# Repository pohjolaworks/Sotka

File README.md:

# Sotka

Split mechanical keyboard with orthogonal layout and detachable extra row

Uses an RJ12 cable for serial communication between the halves.

### Basic layout without extra row

### Reversible PCB with extra row

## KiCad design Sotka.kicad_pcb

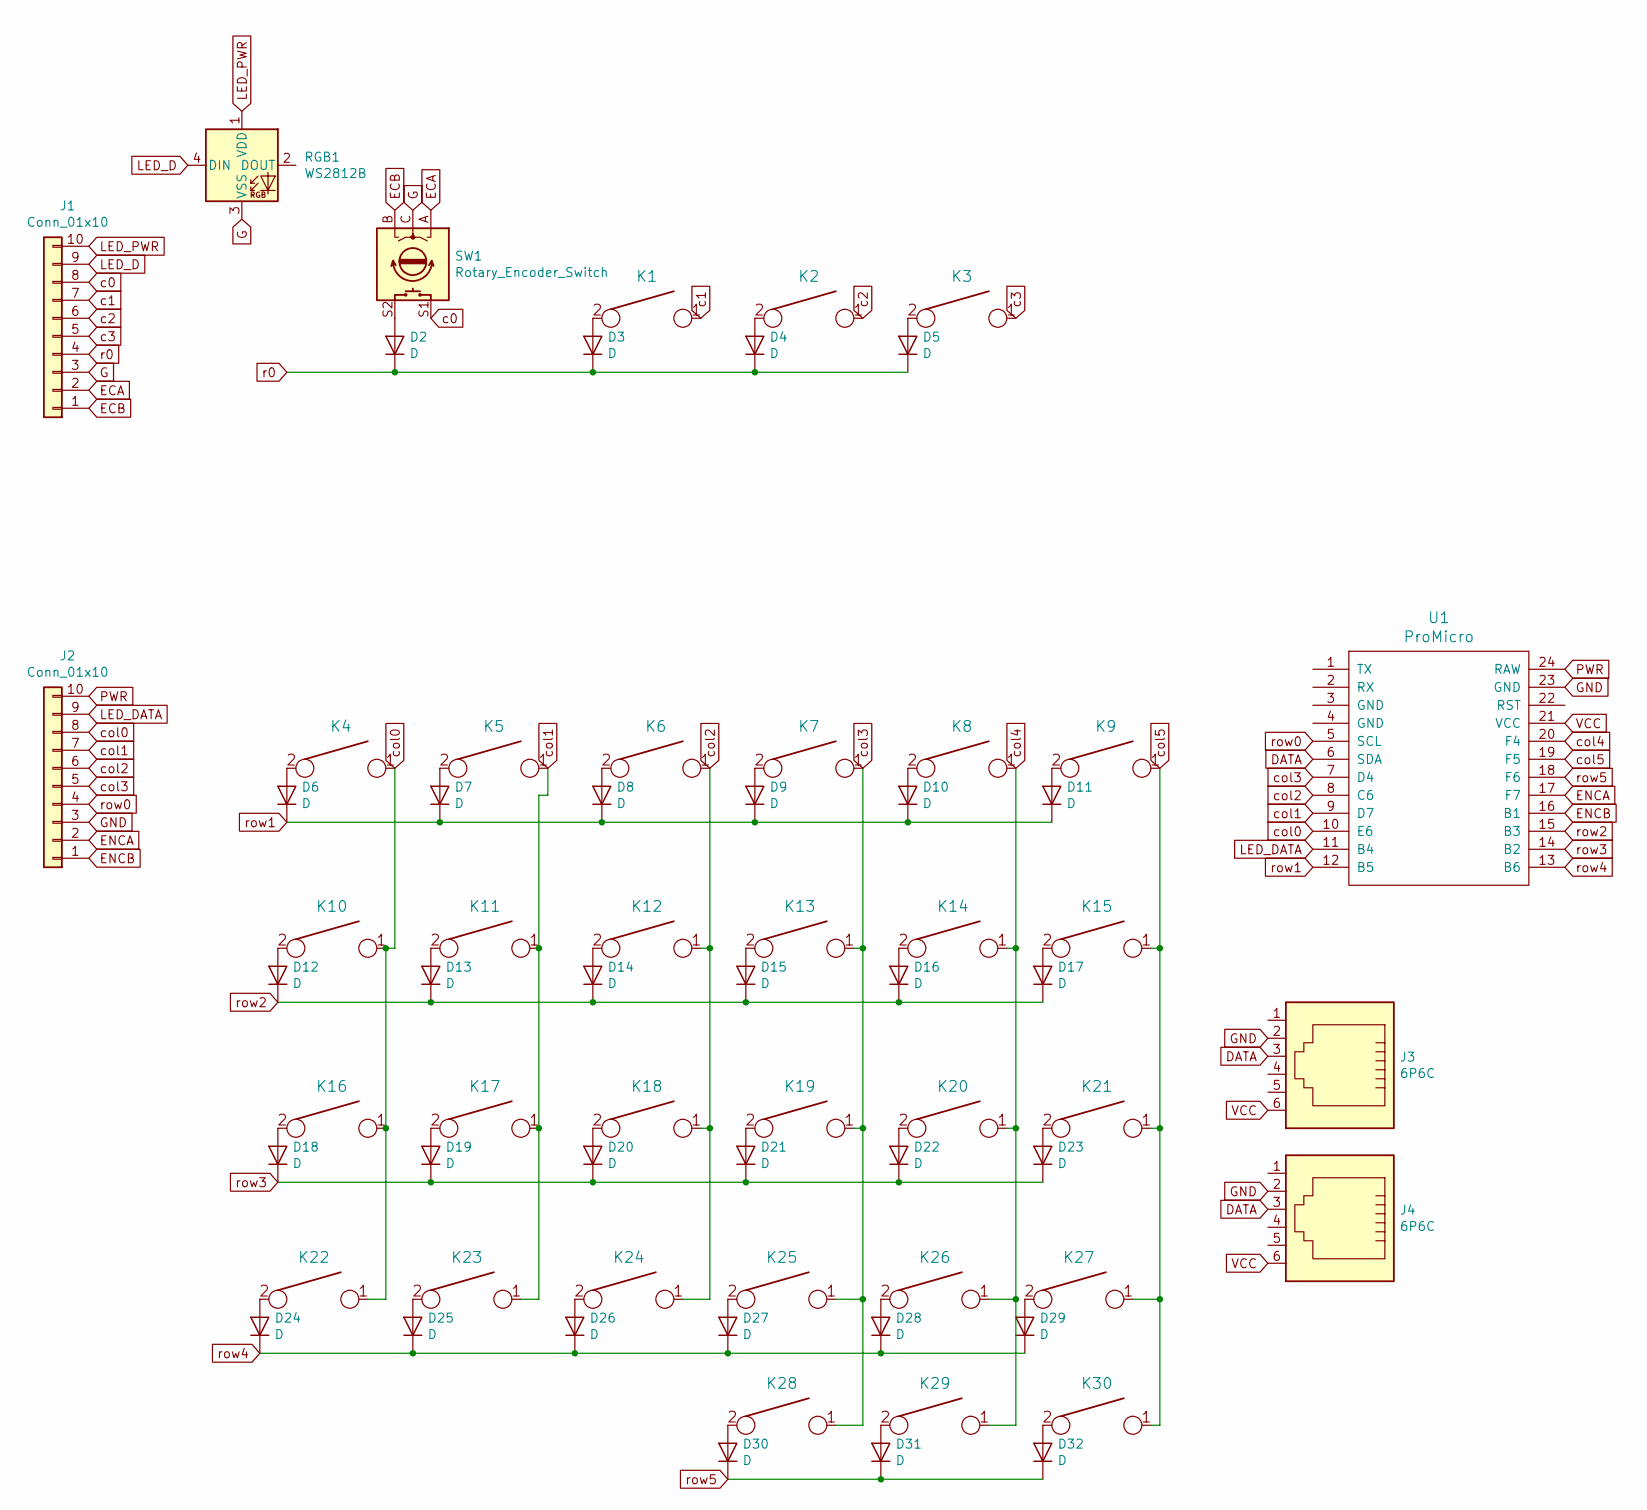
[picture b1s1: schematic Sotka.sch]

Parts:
D2, D3, D4, D5, D6, D7, D8, D9, D10, D11, D12, D13, D14, D15, D16, D17, D18, D19, D20, D21, D22, D23, D24, D25, D26, D27, D28, D29, D30, D31, D32: D; Diode-dual
J1, J2: Conn_01x10; JST_EH_B10B-EH-A_1x10_P2.50mm_Vertical
J3, J4: 6P6C; RJ11-MOLEX
K1, K2, K3, K4, K5, K6, K7, K8, K9, K10, K11, K12, K13, K14, K15, K16, K17, K18, K19, K20, K21, K22, K23, K24, K25, K26, K27, K28, K29, K30: KEYSW; SW_MX_reversible
RGB1: WS2812B; LED_WS2812B_PLCC4_5.0x5.0mm_P3.2mm
SW1: Rotary_Encoder_Switch; RotaryEncoder_Alps_EC11E-Switch_Vertical_H20mm
U1: ProMicro; ArduinoProMicro

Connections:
DATA: J3.3, J4.3, U1.6 (SDA)
ECA: J1.2, SW1.A
ECB: J1.1, SW1.B
ENCA: J2.2, U1.17 (F7)
ENCB: J2.1, U1.16 (B1)
G: J1.3, RGB1.3 (VSS), SW1.C
GND: J2.3, J3.2, J4.2, U1.23 (GND)
LED_D: J1.9, RGB1.4 (DIN)
LED_DATA: J2.9, U1.11 (B4)
LED_PWR: J1.10, RGB1.1 (VDD)
unnamed: D2.2 (A), SW1.S2
unnamed: D3.2 (A), K1.2
unnamed: D4.2 (A), K2.2
unnamed: D5.2 (A), K3.2
unnamed: D6.2 (A), K4.2
unnamed: D7.2 (A), K5.2
unnamed: D8.2 (A), K6.2
unnamed: D9.2 (A), K7.2
unnamed: D10.2 (A), K8.2
unnamed: D11.2 (A), K9.2
unnamed: D12.2 (A), K10.2
unnamed: D13.2 (A), K11.2
unnamed: D14.2 (A), K12.2
unnamed: D15.2 (A), K13.2
unnamed: D16.2 (A), K14.2
unnamed: D17.2 (A), K15.2
unnamed: D18.2 (A), K16.2
unnamed: D19.2 (A), K17.2
unnamed: D20.2 (A), K18.2
unnamed: D21.2 (A), K19.2
unnamed: D22.2 (A), K20.2
unnamed: D23.2 (A), K21.2
unnamed: D24.2 (A), K22.2
unnamed: D25.2 (A), K23.2
unnamed: D26.2 (A), K24.2
unnamed: D27.2 (A), K25.2
unnamed: D28.2 (A), K26.2
unnamed: D29.2 (A), K27.2
unnamed: D30.2 (A), K28.2
unnamed: D31.2 (A), K29.2
unnamed: D32.2 (A), K30.2
PWR: J2.10, U1.24 (RAW)
VCC: J3.6, J4.6, U1.21 (VCC)
c0: J1.8, SW1.S1
c1: J1.7, K1.1
c2: J1.6, K2.1
c3: J1.5, K3.1
col0: J2.8, K4.1, K10.1, K16.1, K22.1, U1.10 (E6)
col1: J2.7, K5.1, K11.1, K17.1, K23.1, U1.9 (D7)
col2: J2.6, K6.1, K12.1, K18.1, K24.1, U1.8 (C6)
col3: J2.5, K7.1, K13.1, K19.1, K25.1, K28.1, U1.7 (D4)
col4: K8.1, K14.1, K20.1, K26.1, K29.1, U1.20 (F4)
col5: K9.1, K15.1, K21.1, K27.1, K30.1, U1.19 (F5)
r0: D2.1 (K), D3.1 (K), D4.1 (K), D5.1 (K), J1.4
row0: J2.4, U1.5 (SCL)
row1: D6.1 (K), D7.1 (K), D8.1 (K), D9.1 (K), D10.1 (K), D11.1 (K), U1.12 (B5)
row2: D12.1 (K), D13.1 (K), D14.1 (K), D15.1 (K), D16.1 (K), D17.1 (K), U1.15 (B3)
row3: D18.1 (K), D19.1 (K), D20.1 (K), D21.1 (K), D22.1 (K), D23.1 (K), U1.14 (B2)
row4: D24.1 (K), D25.1 (K), D26.1 (K), D27.1 (K), D28.1 (K), D29.1 (K), U1.13 (B6)
row5: D30.1 (K), D31.1 (K), D32.1 (K), U1.18 (F6)

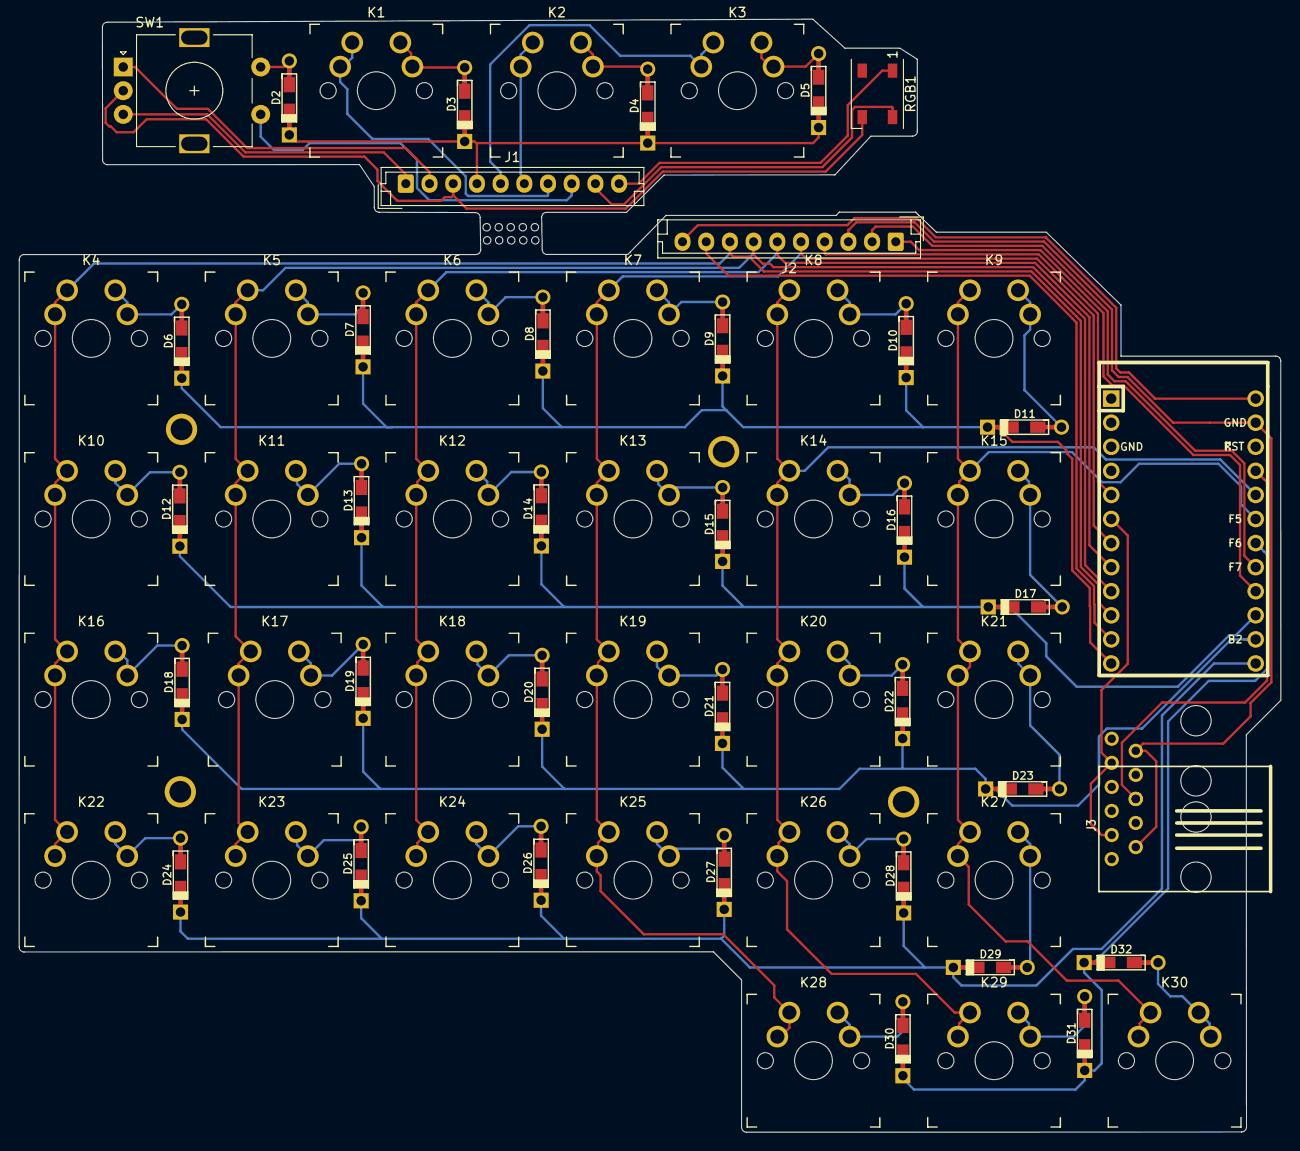
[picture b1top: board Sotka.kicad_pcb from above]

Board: 2 copper layers, 133.1 x 117.4 mm, 72 parts (1 on the bottom side), 60 nets.

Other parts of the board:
HOLE5, HOLE5#2, HOLE5#3, HOLE5#4: MountingHole_4mm; MountingHole_M2

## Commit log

2021-05-07 Rev 0.9
2021-05-07 Add case files & schema
2021-05-07 Add license
2021-05-07 Push readme updates and KLE
2021-05-07 Add moar pics
2021-06-03 Fixed oversized controller cover
2024-06-06 Add assembled keeb to README
2024-06-06 Add assembled pic
